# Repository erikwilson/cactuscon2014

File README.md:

cactuscon2014
=============

# Order of the Cactar

## Purpose

This repository contains the design and documentation for the CactusCon 2014 electronic badge.
The Cactar badge serves the following four functions:

 0. Aesthetically appealing badge earned as reward for community interaction
 0. Ethernet tap
 0. USB 3.0 breakout
 0. Teensy 2.0 mounting option, plus breadboard area

The following sections will explain in greater detail the design and symbology behind the badge.

## Technical Details

Funding for the badge and (free!)
[CactusCon](http://cactuscon.com/speakers) security conference was made possible by generous donations from
[guests](https://www.kickstarter.com/projects/cactuscon/cactuscon-2014) and
[sponsors](http://cactuscon.com/sponsors).
Manufacturing of the badge occured with
[Advanced Circuits](http://www.4pcb.com/) at their Aurora, Colorado facility.
Badges were assembled and tested on site by guests with assistance from members of
[HeatSync Labs](http://heatsynclabs.org/).
Parts for incomplete badges may still be available through
[DigiKey](http://digikey.com/short/952t9).

The Cactar badge design was possible only by
[standing on the shoulders of giants](http://en.wikipedia.org/wiki/Standing_on_the_shoulders_of_giants).
Board design was done with the free version of
[EAGLE](http://www.cadsoftusa.com/download-eagle/). A custom
[ULP](http://www.cadsoftusa.com/downloads/ulps) was created to allow importing of vector graphics from
[Inkscape](http://www.inkscape.org/en/).
Gerber files are viewable through the HTML5 and WebGL renderer at
[MayhewLabs](http://mayhewlabs.com/webGerber/),
make sure optimizations are turned off if in EAGLE when CAM processing for best compatability.

The network tap portion of the badge was made possible due to the fantastic work of
[Michael Ossmann](http://ossmann.blogspot.com/2011/02/throwing-star-lan-tap.html).
Data will flow through ports located on the arms in both directions, while data flows out through the feet.
In this way the feet allow tapping of data and each foot taps data flowing from a different direction.

```
A <> B
V    V
```

The USB 3.0 breakout serves as a general test and hacking tool, stemming from the desire to have a product like the
[USB 2.0 tester](https://www.tindie.com/products/FriedCircuits/usb-tester-20/) for USB 3.0,
and based on experience with the
[PS4 Camera](http://ps4eye.tumblr.com/).

Surrounding the CactusCon logo are holes for mounting a
[Teensy 2.0](http://www.pjrc.com/store/teensy.html) or other micro development board.
The accompanying breadboard area is for general hacking, it can also accomodate small boards such as the
[USB mini host shield](http://www.circuitsathome.com/products-page/arduino-shields/usb-host-shield-for-arduino-pro-mini)
for creation of a
[keylogger](http://www.irongeek.com/i.php?page=security/homemade-hardware-keylogger-phukd).
Another possibility might include mounting an
[ethernet module](http://www.pjrc.com/teensy/td_libs_Ethernet.html)
for analyzing tapped packets through a microprocessor.

## Manifestum

There are several symbols located throughout the CactusCon badge, some of which may be more obvious than others.
Starting at the top, an
[Eye of Providence](http://en.wikipedia.org/wiki/Eye_of_Providence) seems appropriate given the
nature of the badge, as
[knowledge is power](http://en.wikipedia.org/wiki/Information_Awareness_Office).
Radiating from the eye are my initials, EW, as the connected semi-circles and lines beneath the
solder mask.

The symbols
[Tau](http://en.wikipedia.org/wiki/Tau) (τ) and
[Phi](http://en.wikipedia.org/wiki/Phi) (φ) are on either side of the badge.
Tau was chosen because it is
[twice as good as π](http://tauday.com/tau-manifesto), however if you confuse Tau with
[Tao](http://en.wikipedia.org/wiki/Tao) or
[TAO](http://en.wikipedia.org/wiki/Tailored_Access_Operations) that is okay too.
Phi was chosen for the
[Golden Ratio](http://en.wikipedia.org/wiki/Golden_ratio) and the beauty of mathematics in understanding our universe.

Below Tau and Phi and between the USB 3.0 headers is the HeatSync Labs logo.
Next to the copper
[CactusCon](http://cactuscon.com/) logo and silk-screened
[Early Warning](http://earlywarning.com/) and
[Aeris Secure](https://aerissecure.com/) logos is the breadboard area,
with the initials HSL viewable as square pads from the top side, and the adjacent
[heatsynclabs.org](http://heatsynclabs.org/) address present beneath the solder mask.

Located on the top-side right foot is a glider from
[Conway's Game of Life](http://www.bitstorm.org/gameoflife/), chosen as an unofficial
'[hacker](http://www.catb.org/~esr/faqs/hacker-howto.html#attitude)' emblem.
Located on the back-side left foot is a
[Jolly Roger](http://en.wikipedia.org/wiki/Jolly_Roger), chosen to emobody the concept of
[danger and freedom](http://www.unix.org/license-plate.html).

## Fin

Special thanks to [@LosT](https://twitter.com/1o57) for delivering an awesome keynote and creating badges to aspire to.

And especially thanks to all of the guests, presenters, sponsors, and organizers who helped to make this a very special event.

Follow [@CactusCon](https://twitter.com/cactuscon),
       [@HeatSyncLabs](https://twitter.com/heatsynclabs), and
       [@wils0ne](https://twitter.com/wils0ne) for more greatness.

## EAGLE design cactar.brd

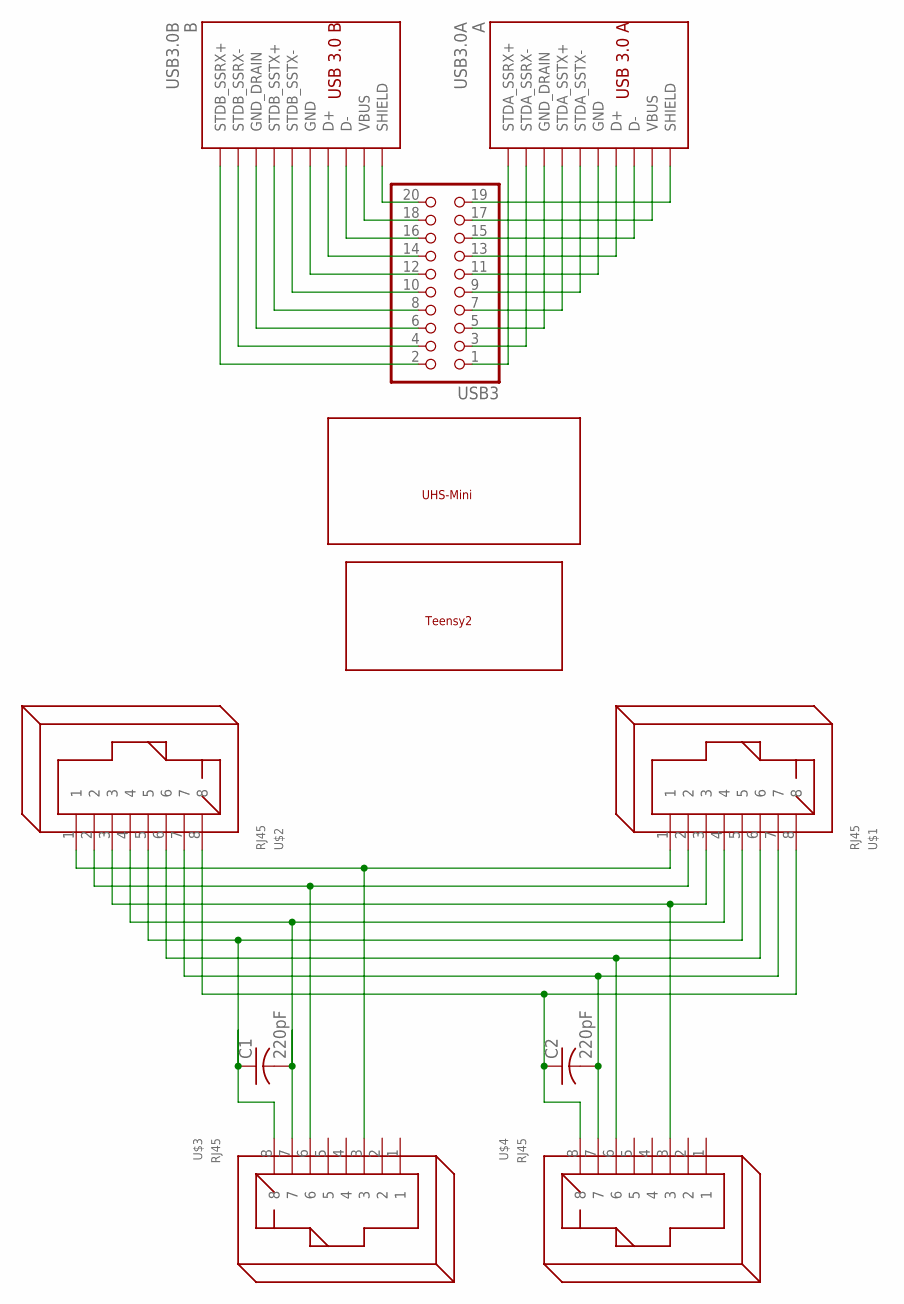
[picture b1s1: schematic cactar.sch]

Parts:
A: USB3.0A; AMPHENOLUSB3.0A
B: USB3.0B; AMPHENOLUSB3.0B
C1, C2: 220pF; C050-025X075
U$1, U$2, U$3, U$4: RJ45
U$5: BREADLY
USB3: PINHD-2X102X10/MIRROR; 2X10/MIRROR
_1: TEENSY2

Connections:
unnamed: U$1.1, U$2.1, U$3.3
unnamed: U$1.2, U$2.2, U$3.6
unnamed: U$1.3, U$2.3, U$4.3
unnamed: C1.2, U$1.4, U$2.4, U$3.7
unnamed: C1.1, U$1.5, U$2.5, U$3.8
unnamed: U$1.6, U$2.6, U$4.6
unnamed: C2.2, U$1.7, U$2.7, U$4.7
unnamed: C2.1, U$1.8, U$2.8, U$4.8
unnamed: B.10@1 (SHIELD), B.10@2 (SHIELD), USB3.20
unnamed: A.10@1 (SHIELD), A.10@2 (SHIELD), USB3.19
unnamed: A.1 (VBUS), USB3.17
unnamed: A.2 (D-), USB3.15
unnamed: A.3 (D+), USB3.13
unnamed: A.4 (GND), USB3.11
unnamed: A.8 (STDA_SSTX-), USB3.9
unnamed: A.9 (STDA_SSTX+), USB3.7
unnamed: A.7 (GND_DRAIN), USB3.5
unnamed: A.5 (STDA_SSRX-), USB3.3
unnamed: A.6 (STDA_SSRX+), USB3.1
unnamed: B.9 (STDB_SSRX+), USB3.2
unnamed: B.8 (STDB_SSRX-), USB3.4
unnamed: B.7 (GND_DRAIN), USB3.6
unnamed: B.6 (STDB_SSTX+), USB3.8
unnamed: B.5 (STDB_SSTX-), USB3.10
unnamed: B.4 (GND), USB3.12
unnamed: B.3 (D+), USB3.14
unnamed: B.2 (D-), USB3.16
unnamed: B.1 (VBUS), USB3.18

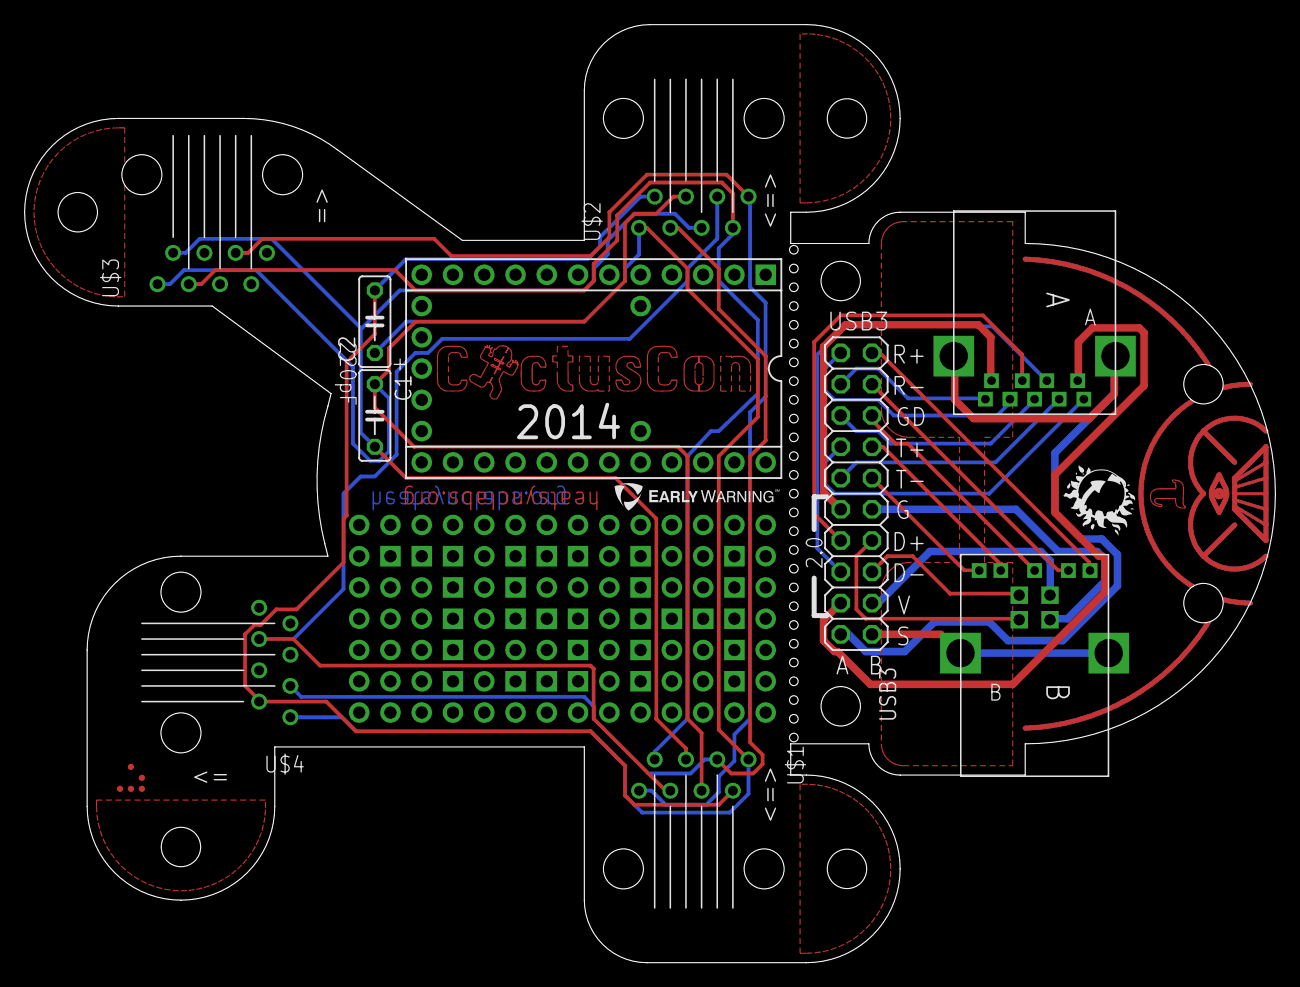
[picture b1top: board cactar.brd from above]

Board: 2 copper layers, 101.6 x 76.2 mm, 11 parts (0 on the bottom side), 28 nets.
